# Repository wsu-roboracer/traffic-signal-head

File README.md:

# 1/10 Scale Traffic Signal Head

LED boards and firmware for a 1/10 scale 12 in (300 mm) three-section traffic
signal head. Both KiCad projects are generated by a script, not hand-drawn —
edit the `VARIANTS` block in [`gen_signal_pcb.py`](gen_signal_pcb.py) and
re-run. UUIDs are deterministic, so regenerating does not churn the files.

```
python gen_signal_pcb.py ring      # signal-head/
python gen_signal_pcb.py dense     # signal-head-dense/
python gen_signal_pcb.py both
```

## Variants

| | [`signal-head/`](signal-head/) | [`signal-head-dense/`](signal-head-dense/) |
|---|---|---|
| LEDs | 36 (12 per lens, 11.5 mm ring) | 57 (19 per lens, filled aperture) |
| Target optics | frosted diffuser, ~15 mm standoff | clear lens, near-zero standoff |
| Per-LED current | 15 mA | 10 mA |
| Peak draw | ~186 mA (green) | ~190 mA |
| Placements | 72, single-sided | 114, single-sided |

The dense variant is **not** an upgrade — it is a different optical design,
where the dots are the visible image rather than a source behind a diffuser.
Each project's README explains the tradeoff and the photometric modelling
behind the layout.

## Electrical

Both boards are common anode, low-side switched, one resistor per LED:

```
VLED (+9 V) --> R(n) --> LED(n) anode
                         LED(n) cathode --> K_RED / K_AMB / K_GRN --> switch --> GND
```

The switch is off-board — a ULN2003A or logic-level MOSFETs. Neither board can
be driven directly from microcontroller or Raspberry Pi GPIO pins: a single
cathode line carries the whole lens (~186 mA), and `VLED` needs 9 V.

## Layout

| | |
|---|---|
| [`gen_signal_pcb.py`](gen_signal_pcb.py) | generator — schematic, board, placement, routing, BOM |
| [`fill_zones.py`](fill_zones.py) | fills the copper pours via `pcbnew` (run automatically) |
| [`make_jlcpcb.py`](make_jlcpcb.py) | gerbers, BOM and CPL for JLCPCB assembly |
| [`firmware/signal_head/`](firmware/signal_head/) | Arduino sketch — phase cycle plus a mode button |

Both boards pass `kicad-cli` ERC and DRC with zero violations and are fully
routed.

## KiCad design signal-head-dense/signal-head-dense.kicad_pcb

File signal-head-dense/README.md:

# 1/10 Scale Traffic Signal Head — LED Board, **dense variant**

57 LEDs, 19 per lens, filling the full 30 mm aperture.

This is the alternative to [`../signal-head/`](../signal-head/), which uses a
single 12-LED ring. Both come from the same generator:

```
python ../gen_signal_pcb.py dense     # this board
python ../gen_signal_pcb.py ring      # the ring variant
python ../gen_signal_pcb.py both
```

## Which variant to build

They are optimised for **different optics**, not different quality levels.

| | ring | dense (this one) |
|---|---|---|
| LEDs | 36 (12/lens) | **57 (19/lens)** |
| Resistors | 36 × 0805 | 57 × **0603** |
| Lens | frosted **diffuser** | **clear or lightly tinted** |
| Standoff | ~15 mm | near zero |
| Uniformity, 24 mm aperture | **~86%** | 64% |
| Look | even glowing disc | **visible dot array** |
| Peak current | ~186 mA | ~207 mA |
| SMD placements | 72 | **114** |
| J1 | front | back |

A 12-LED ring already over-lights the lens centre, so on a diffused board
adding interior LEDs measurably *hurts* uniformity — see the analysis in the
[ring README](../signal-head/README.md#why-the-ring-has-no-interior-leds).

So this board is not for use behind a diffuser. It is for the other design:
**the LEDs are the visible image**, the way a real modern 12 in LED signal
module works. There the array has to fill the aperture, because you are looking
straight at the dots. Uniformity of a notional diffused disc is irrelevant.

## Board

| | |
|---|---|
| Size | **35.6 × 106.7 mm** (1/10 of the 14 × 42 in signal face) |
| Lens centers | 17.8 / 53.4 / 89.0 mm from the top edge |
| LEDs | 57 × `LED_0805_2012Metric` (**KENTO KT-0805**), front: **1 centre + 6 @ r=6.0 + 12 @ r=11.5 mm** |
| Resistors | 57 × `R_0603_1608Metric` (**0603, 1.6 × 0.8 mm**), **front**, r=15.5 mm |
| Connector | J1, 4-pin 2.54 mm header, **back** |
| Mounting | 4 × M2 (2.2 mm), 3 mm in from each corner |
| Layers | 2 — the back carries the VLED pour and J1 only |

**Every placed SMD part is on the front.** Single-sided placement is one
assembly setup instead of two. J1 is through-hole, so it takes no part in the
SMD run and sitting on the back costs nothing.

Dot spacing comes out close to even, which is what sells the look:

| | |
|---|---|
| centre → inner ring | 6.00 mm |
| inner ring neighbours | 6.28 mm |
| inner → outer ring | 5.50 mm |
| outer ring neighbours | 6.02 mm |
| outer LED pad edge | r = 13.50 mm (1.5 mm inside the aperture) |

### Why 0603 here and 0805 on the ring board

Not a preference — a constraint, twice over.

**Thermal.** At ~10 mA these dissipate up to 0.062 W, which is 62% of 0603's
0.100 W rating. The ring board's legs dissipate 0.089 W, which would be 89% of
0603 and 142% of 0402 — so that board stays on 0805. Going below 0603 here is also out:
0402 would run at 90% of rating.

**Area.** The dense front has no interior room left, so all 57 resistors have to
live on a rim outside the LED rings. 0805's courtyard forced either the LED
rings inward (shrinking the dot field) or the resistors outward to within
0.75 mm of the board edge. 0603's smaller courtyard is what lets the rings stay
at full aperture fill with a clean 1.08 mm edge margin.

Package size does not change machine-assembly cost, only board area and thermal
headroom.

### Why J1 is on the back

The resistor rim rings leave only **1.6 mm** between adjacent lenses on the
front — not enough for a connector. The back is otherwise empty, and a
through-hole part is a separate soldering operation regardless of side, so
nothing is lost.

## Electrical

Identical topology to the ring variant — common anode, low-side switched,
one resistor per LED:

```
VLED (+9 V) --> R(n) --> LED(n) anode
                         LED(n) cathode --> K_RED / K_AMB / K_GRN --> switch --> GND
```

| Net | Nodes | |
|---|---|---|
| `VLED` | 58 | 57 resistors + J1.1 |
| `K_RED` | 20 | 19 cathodes + J1.2 |
| `K_AMB` | 20 | 19 cathodes + J1.3 |
| `K_GRN` | 20 | 19 cathodes + J1.4 |
| `A1`–`A57` | 2 each | one resistor to one LED anode |

**Values are lower-current than the ring variant on purpose.** 19 LEDs at the
ring board's 15 mA would be 285 mA — too much for a 9 V PP3. Dropping to ~10 mA
keeps peak draw level with the 12-LED board while putting 58% more emitters
behind the lens:

| Color | Part | LCSC | Vf | R | Actual | Per lens | Dissipation |
|---|---|---|---|---|---|---|---|
| Red, D1–D19 | KT-0805R | **C2295** | 2.4 V | 560 Ω | 10.0 mA | 190 mA | 0.056 W (56%) |
| Amber, D20–D38 | KT-0805Y | **C2296** | 2.1 V | 560 Ω | 10.5 mA | 200 mA | 0.062 W (62%) |
| Green, D39–D57 | KT-0805G | **C2297** | 2.9 V | 470 Ω | 10.9 mA | 207 mA | 0.055 W (55%) |

Assumes a ULN2003A with ~1 V saturation drop.

Only one color is lit at a time: **~207 mA peak** (green). Part selection and brightness figures are in the [ring README](../signal-head/README.md#parts--jlcpcb).

## Verification

```
sch erc  ->  0 violations
pcb drc  ->  0 violations, schematic parity 0
```

The 171 reported "unconnected items" are the **intentionally unrouted**
ratsnest: 57 anodes + 3 × 19 cathodes + 57 VLED pads (the last 57 disappear
once the back zone is filled and the VLED vias are placed).

## What is left to do

1. **Fill zones** — open the PCB and press `B`.
2. **Route.** Radii from each lens centre; all LED and resistor pads are on the
   front. Unlike the ring board, anodes face **outboard** here, toward the
   resistor rim:

   | | r |
   |---|---|
   | Centre LED cathode / anode | 0.9375 mm either side |
   | Inner-ring cathode / anode | 5.0625 / 6.9375 mm |
   | Outer-ring cathode / anode | **10.5625** / 12.4375 mm |
   | Resistor inner / outer pads | 14.675 / 16.325 mm |

   - **Outer 12 anodes** are easy: a straight radial track from the anode pad
     to its resistor's inner pad, 1.825 mm of clear gap, no via.
   - **Centre and inner 6 anodes** are the awkward ones — they have to get past
     the outer LED ring. The inner LEDs sit at 60° spacing and the outer ones
     at 30°, so each inner LED is radially *aligned* with an outer one and the
     direct path is blocked. Either thread diagonally through the 3.82 mm
     tangential gaps at ±15°, or drop a via and run these seven on the back,
     which is far easier since the back is empty.
   - **Cathodes**: three groups per lens — the centre pad, a hexagon through the
     six inner cathode pads at r = 5.0625 mm, and a 12-gon through the outer
     cathode pads at r = 10.5625 mm. Pads sit exactly on those radii.
   - **VLED**: a 19-gon through the resistor outer pads at r = 16.325 mm, plus
     one via per lens to the back pour. J1's VLED pin is through-hole and
     touches the pour directly.
3. **Lens choice.** This board wants a clear or lightly tinted lens at near-zero
   standoff. Putting it behind a frosted diffuser throws away the reason it
   exists and gives worse uniformity than the ring board.
4. **White soldermask** still helps, though less than on the ring board, since
   far less light reaches the substrate between dots.

## Fab notes

Same 35.6 × 106.7 mm size as the ring variant, so the same 100 × 100 mm budget
tier overrun applies. Reference designators on D*, R*, and H* are hidden on
silkscreen (57 parts per lens area makes them unreadable; they remain on F.Fab
for assembly).

**Assembly cost is the real difference** — 114 placements versus 72. If you are
paying for turnkey assembly, this variant is roughly 60% more per board, though
both are now single-sided.

## Files

| File | |
|---|---|
| `signal-head-dense.kicad_pro` | project |
| `signal-head-dense.kicad_sch` | schematic, 119 symbols |
| `signal-head-dense.kicad_pcb` | board, placed and netted |
| `bom.csv` | grouped bill of materials |
| `top.png` / `bottom.png` | renders |
| `erc.rpt` / `drc.json` | verification output |

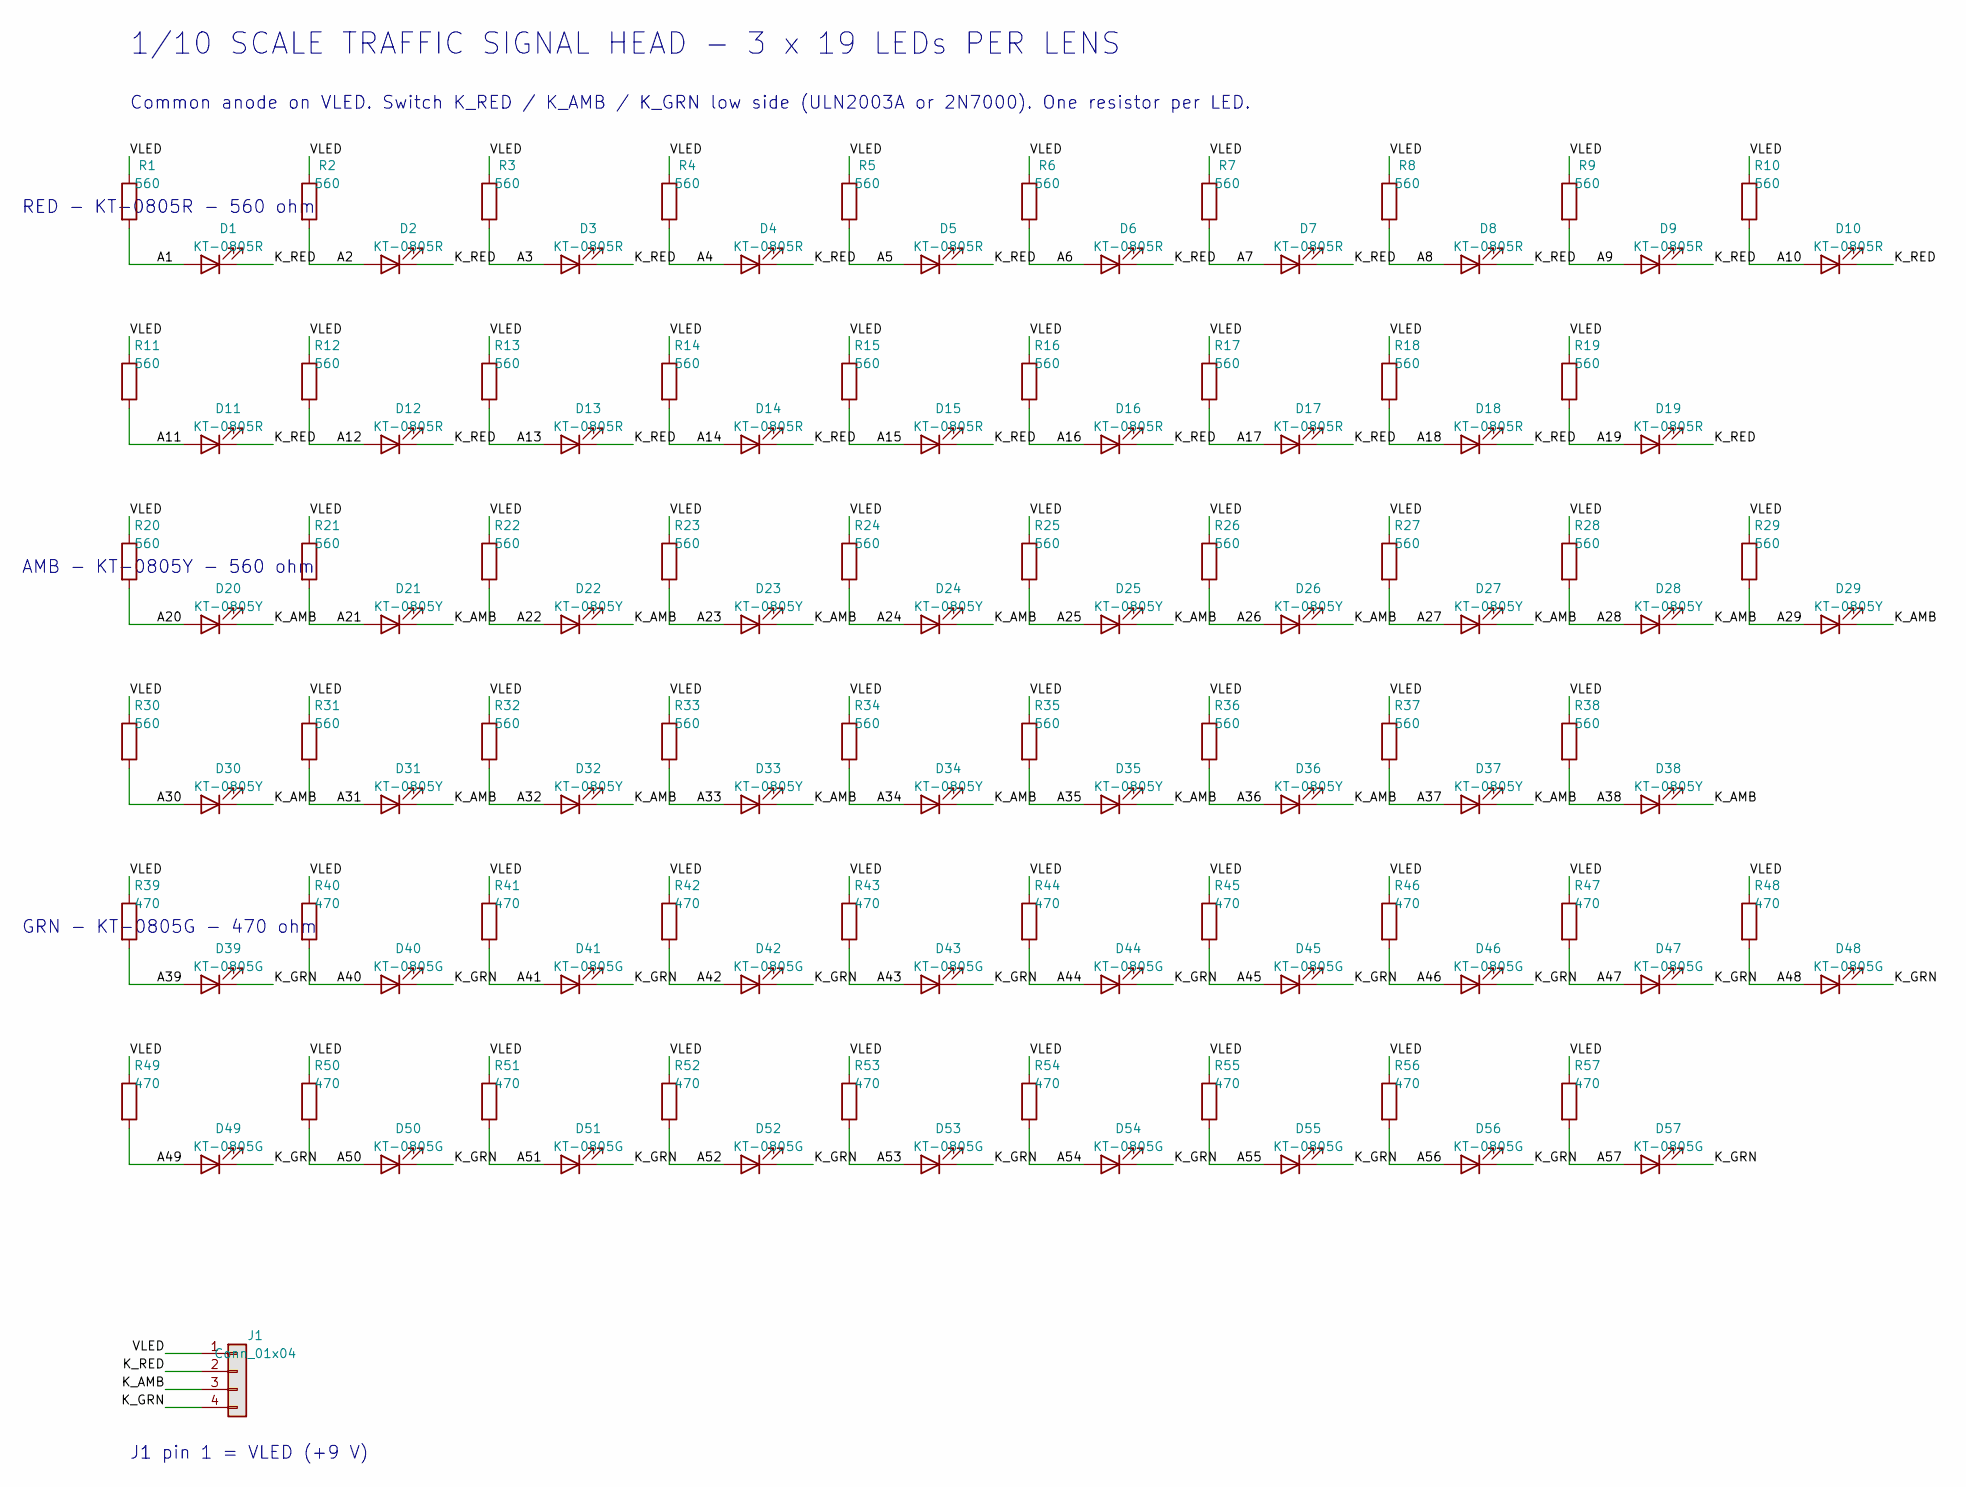
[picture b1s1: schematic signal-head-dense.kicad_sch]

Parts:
D1, D2, D3, D4, D5, D6, D7, D8, D9, D10, D11, D12, D13, D14, D15, D16, D17, D18, D19: KT-0805R; LED_0805_2012Metric; LCSC C2295
D20, D21, D22, D23, D24, D25, D26, D27, D28, D29, D30, D31, D32, D33, D34, D35, D36, D37, D38: KT-0805Y; LED_0805_2012Metric; LCSC C2296
D39, D40, D41, D42, D43, D44, D45, D46, D47, D48, D49, D50, D51, D52, D53, D54, D55, D56, D57: KT-0805G; LED_0805_2012Metric; LCSC C2297
J1: Conn_01x04; PinHeader_1x04_P2.54mm_Vertical
R1, R2, R3, R4, R5, R6, R7, R8, R9, R10, R11, R12, R13, R14, R15, R16, R17, R18, R19, R20, R21, R22, R23, R24, R25, R26, R27, R28, R29, R30, R31, R32, R33, R34, R35, R36, R37, R38: 560; R_0603_1608Metric; LCSC C23204
R39, R40, R41, R42, R43, R44, R45, R46, R47, R48, R49, R50, R51, R52, R53, R54, R55, R56, R57: 470; R_0603_1608Metric; LCSC C23179

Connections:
A1: D1.2 (A), R1.2
A2: D2.2 (A), R2.2
A3: D3.2 (A), R3.2
A4: D4.2 (A), R4.2
A5: D5.2 (A), R5.2
A6: D6.2 (A), R6.2
A7: D7.2 (A), R7.2
A8: D8.2 (A), R8.2
A9: D9.2 (A), R9.2
A10: D10.2 (A), R10.2
A11: D11.2 (A), R11.2
A12: D12.2 (A), R12.2
A13: D13.2 (A), R13.2
A14: D14.2 (A), R14.2
A15: D15.2 (A), R15.2
A16: D16.2 (A), R16.2
A17: D17.2 (A), R17.2
A18: D18.2 (A), R18.2
A19: D19.2 (A), R19.2
A20: D20.2 (A), R20.2
A21: D21.2 (A), R21.2
A22: D22.2 (A), R22.2
A23: D23.2 (A), R23.2
A24: D24.2 (A), R24.2
A25: D25.2 (A), R25.2
A26: D26.2 (A), R26.2
A27: D27.2 (A), R27.2
A28: D28.2 (A), R28.2
A29: D29.2 (A), R29.2
A30: D30.2 (A), R30.2
A31: D31.2 (A), R31.2
A32: D32.2 (A), R32.2
A33: D33.2 (A), R33.2
A34: D34.2 (A), R34.2
A35: D35.2 (A), R35.2
A36: D36.2 (A), R36.2
A37: D37.2 (A), R37.2
A38: D38.2 (A), R38.2
A39: D39.2 (A), R39.2
A40: D40.2 (A), R40.2
A41: D41.2 (A), R41.2
A42: D42.2 (A), R42.2
A43: D43.2 (A), R43.2
A44: D44.2 (A), R44.2
A45: D45.2 (A), R45.2
A46: D46.2 (A), R46.2
A47: D47.2 (A), R47.2
A48: D48.2 (A), R48.2
A49: D49.2 (A), R49.2
A50: D50.2 (A), R50.2
A51: D51.2 (A), R51.2
A52: D52.2 (A), R52.2
A53: D53.2 (A), R53.2
A54: D54.2 (A), R54.2
A55: D55.2 (A), R55.2
A56: D56.2 (A), R56.2
A57: D57.2 (A), R57.2
K_AMB: D20.1 (K), D21.1 (K), D22.1 (K), D23.1 (K), D24.1 (K), D25.1 (K), D26.1 (K), D27.1 (K), D28.1 (K), D29.1 (K), D30.1 (K), D31.1 (K), D32.1 (K), D33.1 (K), D34.1 (K), D35.1 (K), D36.1 (K), D37.1 (K), D38.1 (K), J1.3
K_GRN: D39.1 (K), D40.1 (K), D41.1 (K), D42.1 (K), D43.1 (K), D44.1 (K), D45.1 (K), D46.1 (K), D47.1 (K), D48.1 (K), D49.1 (K), D50.1 (K), D51.1 (K), D52.1 (K), D53.1 (K), D54.1 (K), D55.1 (K), D56.1 (K), D57.1 (K), J1.4
K_RED: D1.1 (K), D2.1 (K), D3.1 (K), D4.1 (K), D5.1 (K), D6.1 (K), D7.1 (K), D8.1 (K), D9.1 (K), D10.1 (K), D11.1 (K), D12.1 (K), D13.1 (K), D14.1 (K), D15.1 (K), D16.1 (K), D17.1 (K), D18.1 (K), D19.1 (K), J1.2
VLED: J1.1, R1.1, R2.1, R3.1, R4.1, R5.1, R6.1, R7.1, R8.1, R9.1, R10.1, R11.1, R12.1, R13.1, R14.1, R15.1, R16.1, R17.1, R18.1, R19.1, R20.1, R21.1, R22.1, R23.1, R24.1, R25.1, R26.1, R27.1, R28.1, R29.1, R30.1, R31.1, R32.1, R33.1, R34.1, R35.1, R36.1, R37.1, R38.1, R39.1, R40.1, R41.1, R42.1, R43.1, R44.1, R45.1, R46.1, R47.1, R48.1, R49.1, R50.1, R51.1, R52.1, R53.1, R54.1, R55.1, R56.1, R57.1

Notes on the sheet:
1/10 SCALE TRAFFIC SIGNAL HEAD - 3 x 19 LEDs PER LENS
Common anode on VLED. Switch K_RED / K_AMB / K_GRN low side (ULN2003A or 2N7000). One resistor per LED.
RED - KT-0805R - 560 ohm
AMB - KT-0805Y - 560 ohm
GRN - KT-0805G - 470 ohm
J1 pin 1 = VLED (+9 V)

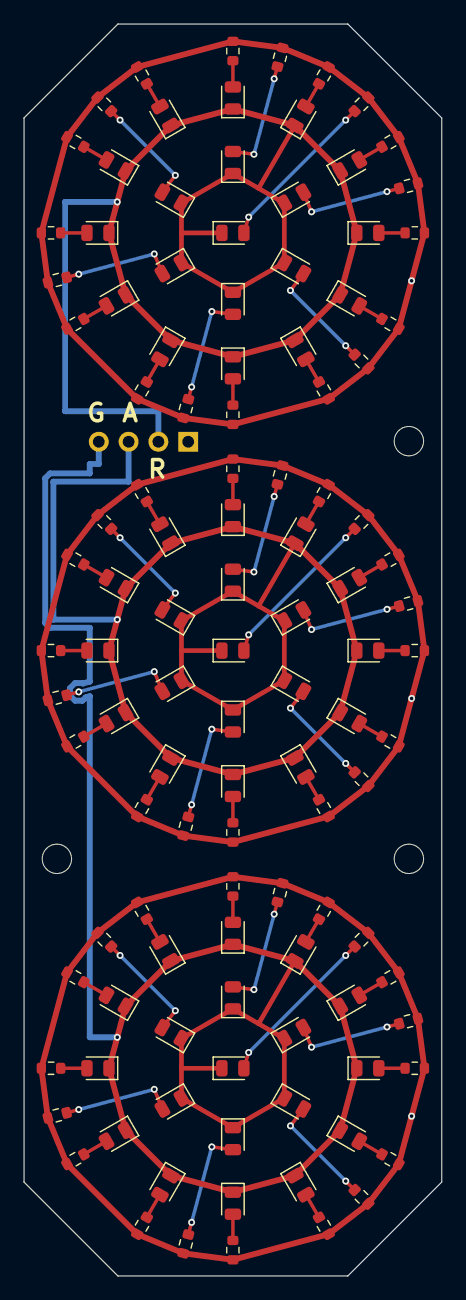
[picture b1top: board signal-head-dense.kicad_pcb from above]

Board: 2 copper layers, 35.6 x 106.7 mm, 115 parts (1 on the bottom side), 61 nets.

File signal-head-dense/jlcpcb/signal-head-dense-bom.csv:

Comment,Designator,Footprint,LCSC Part #
KT-0805R,"D1,D2,D3,D4,D5,D6,D7,D8,D9,D10,D11,D12,D13,D14,D15,D16,D17,D18,D19",LED_0805_2012Metric,C2295
KT-0805Y,"D20,D21,D22,D23,D24,D25,D26,D27,D28,D29,D30,D31,D32,D33,D34,D35,D36,D37,D38",LED_0805_2012Metric,C2296
KT-0805G,"D39,D40,D41,D42,D43,D44,D45,D46,D47,D48,D49,D50,D51,D52,D53,D54,D55,D56,D57",LED_0805_2012Metric,C2297
560,"R1,R2,R3,R4,R5,R6,R7,R8,R9,R10,R11,R12,R13,R14,R15,R16,R17,R18,R19,R20,R21,R22,R23,R24,R25,R26,R27,R28,R29,R30,R31,R32,R33,R34,R35,R36,R37,R38",R_0603_1608Metric,C23204
470,"R39,R40,R41,R42,R43,R44,R45,R46,R47,R48,R49,R50,R51,R52,R53,R54,R55,R56,R57",R_0603_1608Metric,C23179
